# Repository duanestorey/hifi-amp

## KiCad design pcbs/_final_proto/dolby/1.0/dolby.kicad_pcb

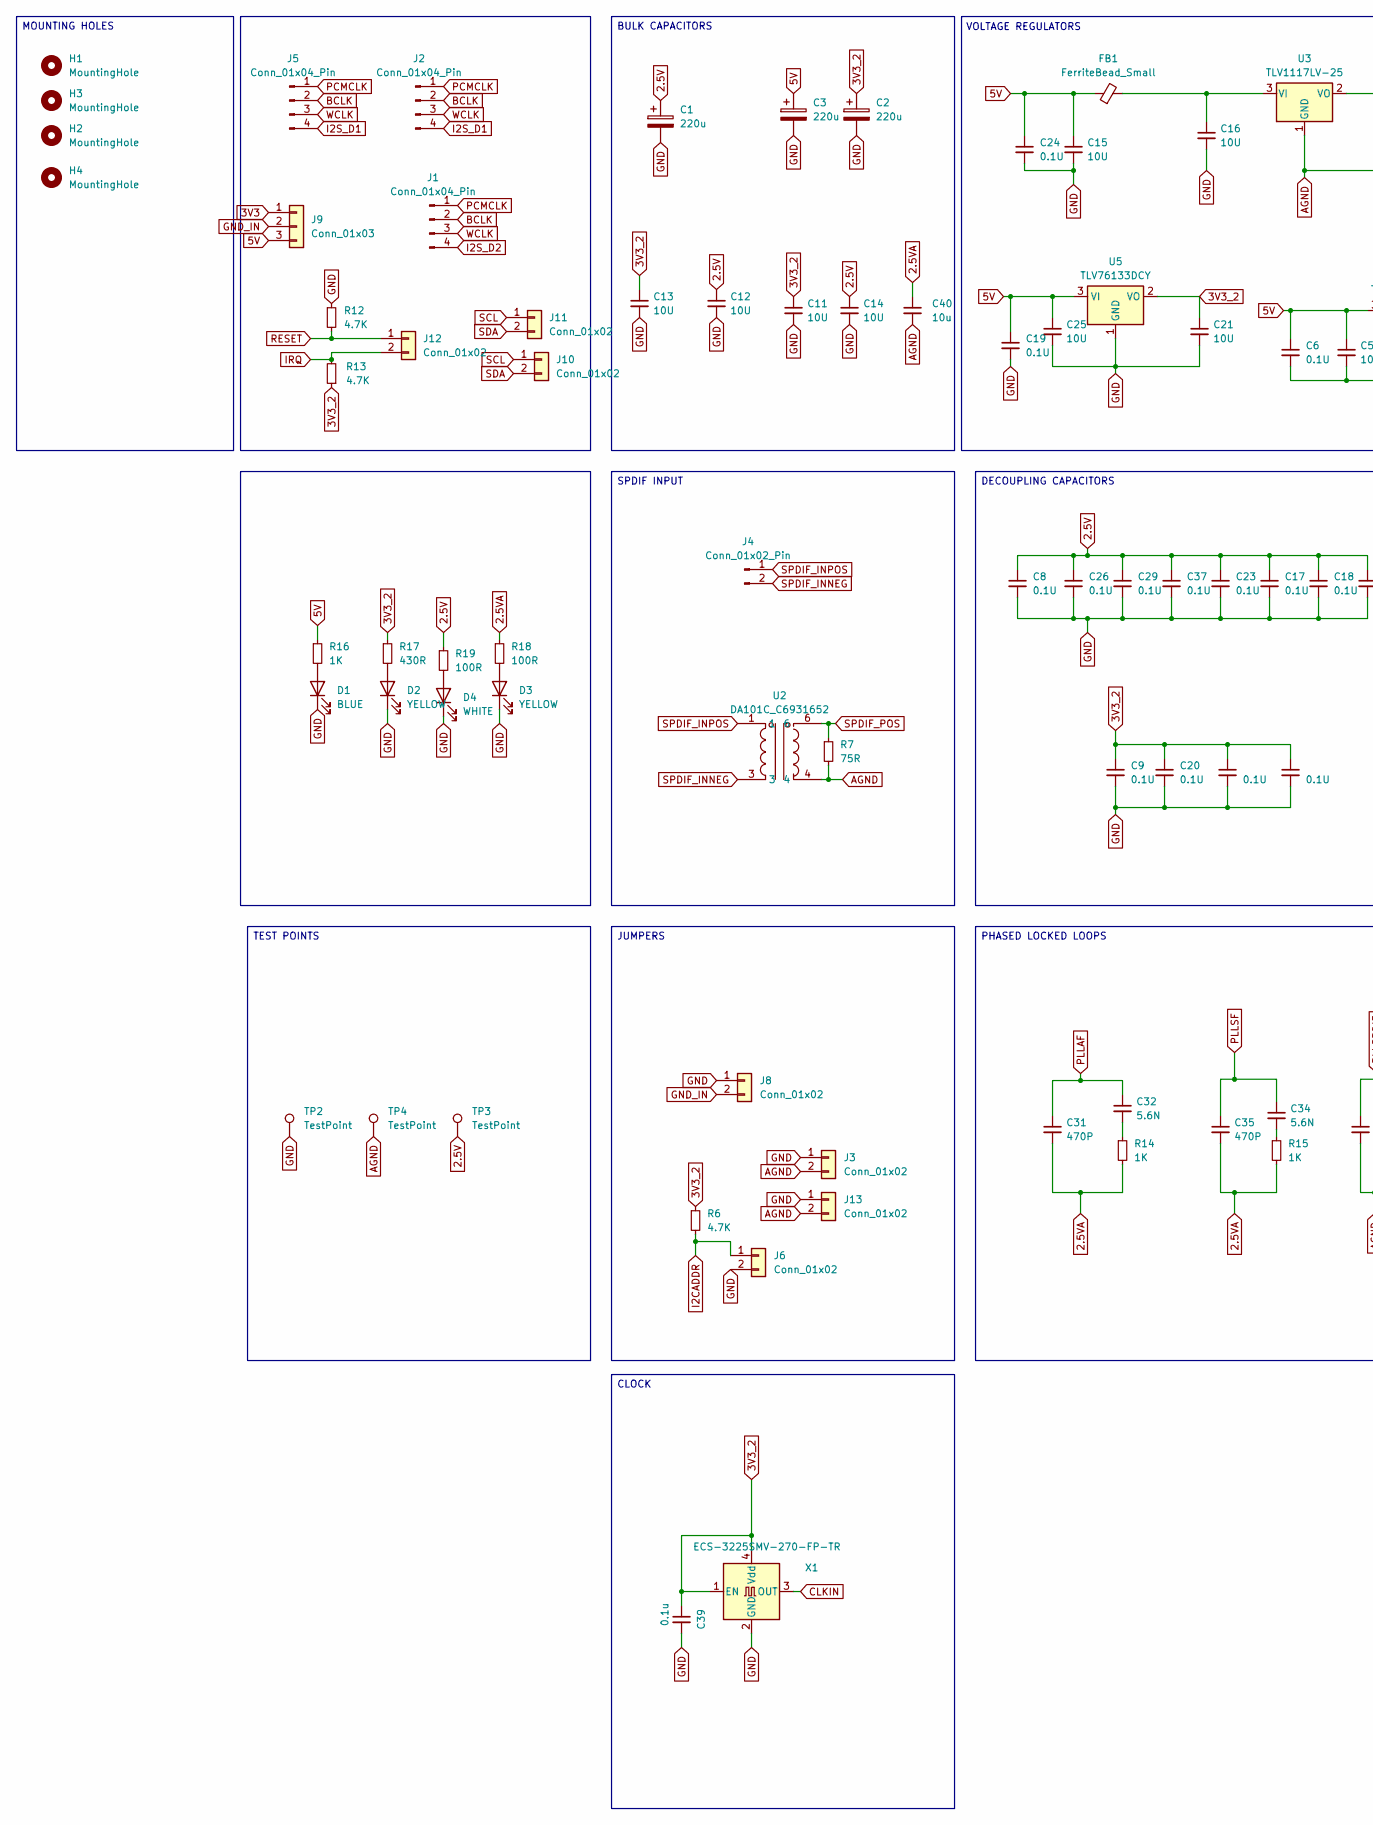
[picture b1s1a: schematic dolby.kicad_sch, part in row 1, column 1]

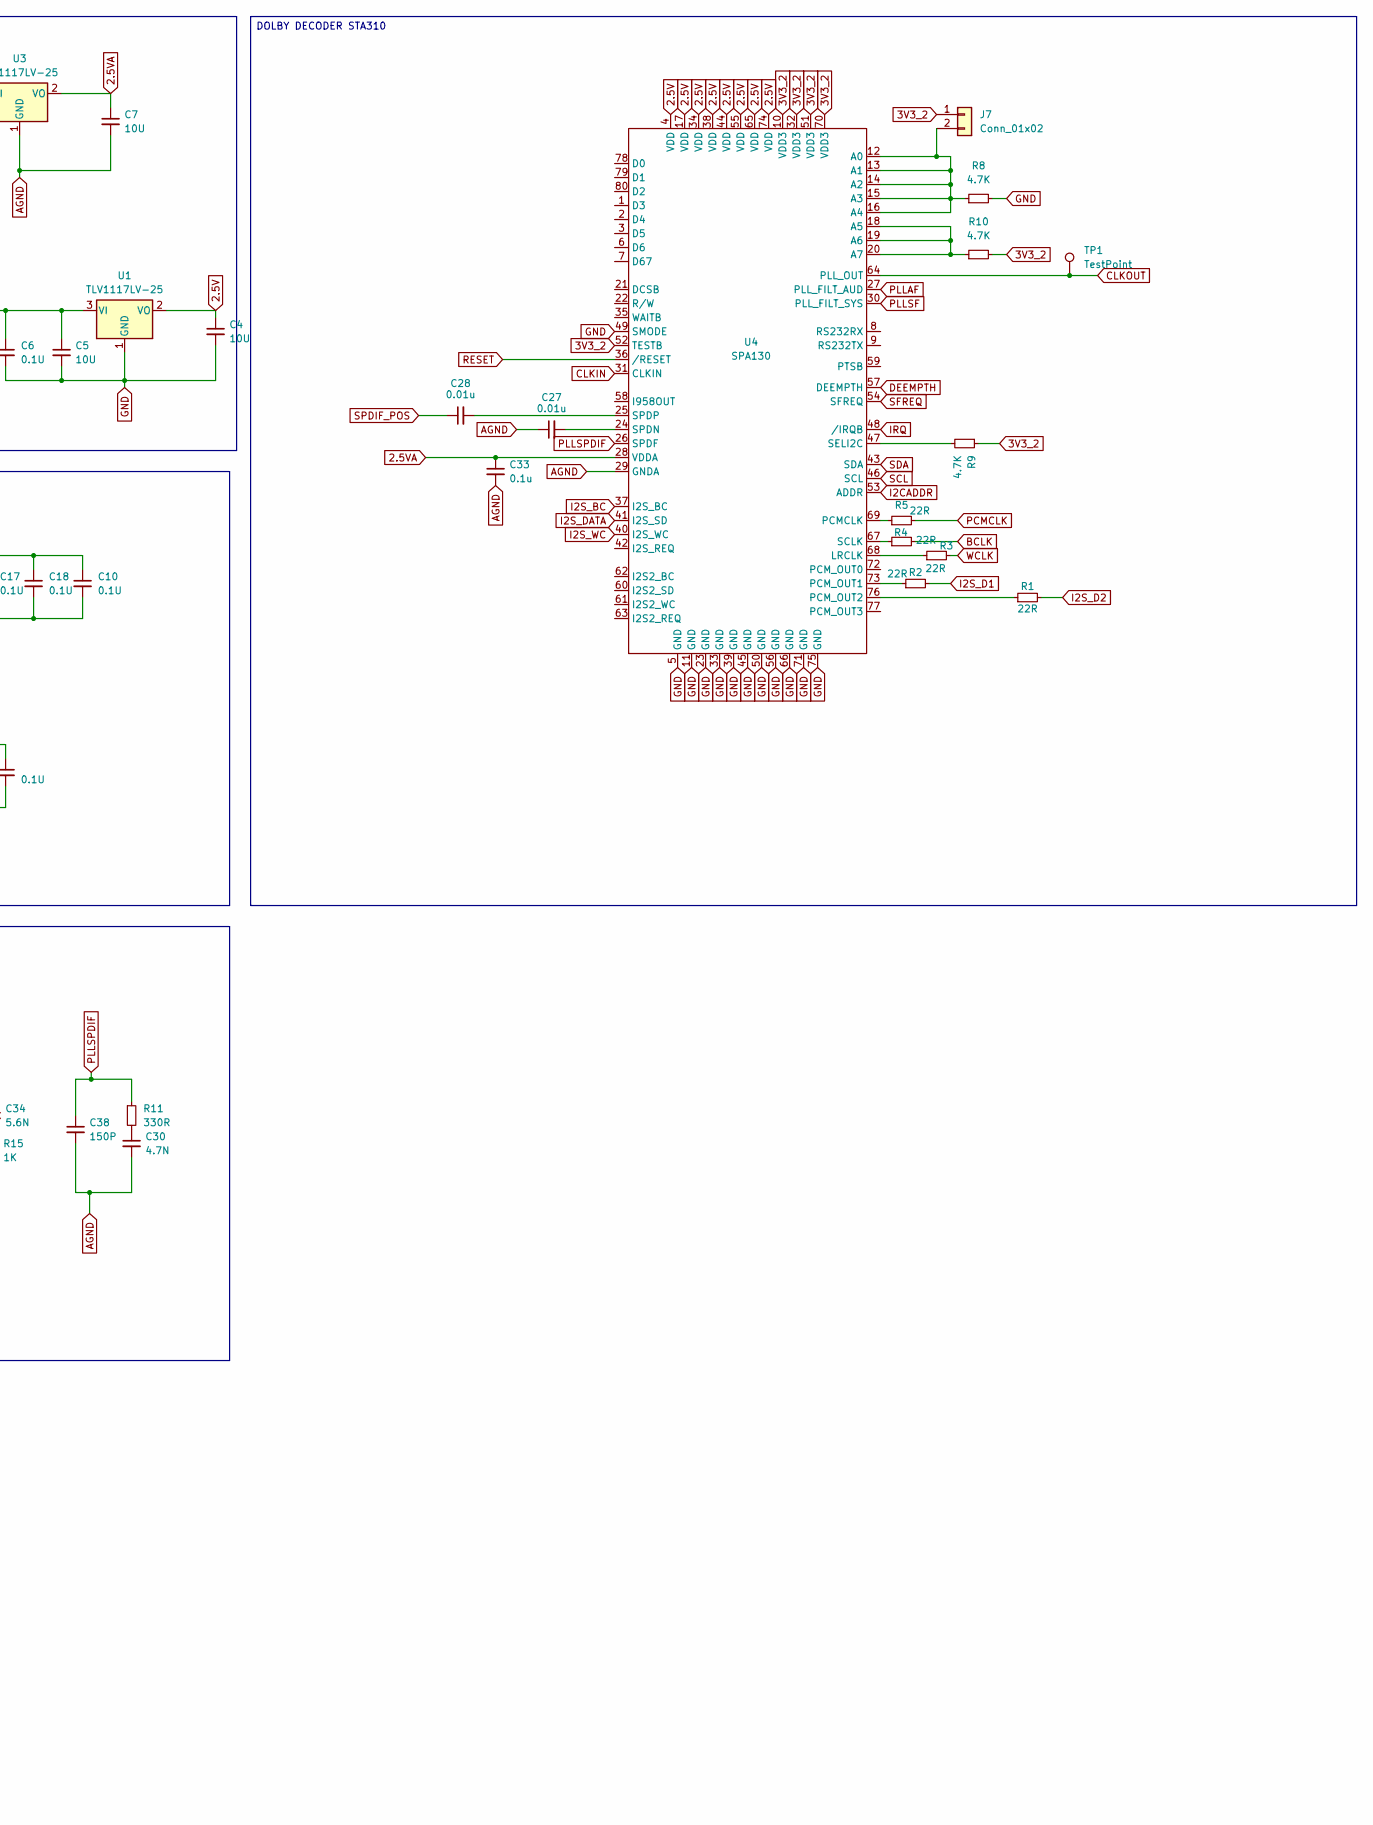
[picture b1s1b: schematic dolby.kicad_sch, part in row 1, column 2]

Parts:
C1, C2, C3: 220u; CP_Radial_D6.3mm_P2.50mm
C4, C5, C7, C11, C12, C13, C14, C15, C16, C21, C25: 10U; C_1206_3216Metric_Pad1.33x1.80mm_HandSolder
C6, C8, C9, C10, C17, C18, C19, C20, C22, C23, C24, C26, C29, C36, C37: 0.1U; C_0805_2012Metric_Pad1.18x1.45mm_HandSolder
C27, C28: 0.01u; C_0805_2012Metric_Pad1.18x1.45mm_HandSolder
C30: 4.7N; C_0805_2012Metric_Pad1.18x1.45mm_HandSolder
C31, C35: 470P; C_0805_2012Metric_Pad1.18x1.45mm_HandSolder
C32, C34: 5.6N; C_0805_2012Metric_Pad1.18x1.45mm_HandSolder
C33, C39: 0.1u; C_0805_2012Metric_Pad1.18x1.45mm_HandSolder
C38: 150P; C_0805_2012Metric_Pad1.18x1.45mm_HandSolder
C40: 10u; C_1206_3216Metric_Pad1.33x1.80mm_HandSolder
D1: BLUE; LED_0805_2012Metric_Pad1.15x1.40mm_HandSolder
D2, D3: YELLOW; LED_0805_2012Metric_Pad1.15x1.40mm_HandSolder
D4: WHITE; LED_0805_2012Metric_Pad1.15x1.40mm_HandSolder
FB1: FerriteBead_Small; R_0603_1608Metric_Pad0.98x0.95mm_HandSolder
H1, H2, H3, H4: MountingHole; MountingHole_3.2mm_M3_DIN965_Pad_TopBottom
J1, J2: Conn_01x04_Pin; JST_PH_B4B-PH-K_1x04_P2.00mm_Vertical
J3, J6, J7, J8, J13: Conn_01x02; PinHeader_1x02_P2.54mm_Vertical
J4: Conn_01x02_Pin; JST_XH_B2B-XH-A_1x02_P2.50mm_Vertical
J5: Conn_01x04_Pin; PinHeader_1x04_P2.54mm_Vertical
J9: Conn_01x03; JST_PH_B3B-PH-K_1x03_P2.00mm_Vertical
J10, J11, J12: Conn_01x02; JST_PH_B2B-PH-K_1x02_P2.00mm_Vertical
R1, R2, R3, R4, R5: 22R; R_0805_2012Metric_Pad1.20x1.40mm_HandSolder
R6, R8, R9, R10, R12, R13: 4.7K; R_0603_1608Metric_Pad0.98x0.95mm_HandSolder
R7: 75R; R_0805_2012Metric_Pad1.20x1.40mm_HandSolder
R11: 330R; R_0603_1608Metric_Pad0.98x0.95mm_HandSolder
R14, R15: 1K; R_0603_1608Metric_Pad0.98x0.95mm_HandSolder
R16: 1K; R_0805_2012Metric_Pad1.20x1.40mm_HandSolder
R17: 430R; R_0805_2012Metric_Pad1.20x1.40mm_HandSolder
R18, R19: 100R; R_0805_2012Metric_Pad1.20x1.40mm_HandSolder
TP1, TP2, TP3, TP4: TestPoint; TestPoint_THTPad_D2.0mm_Drill1.0mm
U1, U3: TLV1117LV-25; SOT-223-3_TabPin2
U2: DA101C_C6931652; XFMR-TH_4P-L9.5-W9.0-P5.08-LS10.2_C9900096976; LCSC Part C6931652
U4: SPA130; LQFP-80_14x14mm_P0.65mm
U5: TLV76133DCY; SOT-223-3_TabPin2
X1: ECS-3225SMV-270-FP-TR; Oscillator_SMD_EuroQuartz_XO32-4Pin_3.2x2.5mm_HandSoldering

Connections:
2.5V: C1.1, C4.1, C8.1, C10.1, C12.1, C14.1, C17.1, C18.1, C23.1, C26.1, C29.1, C37.1, R19.1, TP3.1, U1.2 (VO), U4.4 (VDD), U4.17 (VDD), U4.34 (VDD), U4.38 (VDD), U4.44 (VDD), U4.55 (VDD), U4.65 (VDD), U4.74 (VDD)
2.5VA: C7.1, C31.2, C33.1, C35.2, C40.1, R14.2, R15.2, R18.1, U3.2 (VO), U4.28 (VDDA)
3V3: J9.1
3V3_2: C2.1, C9.1, C11.1, C13.1, C20.1, C21.1, C22.1, C36.1, C39.1, J7.1, R6.1, R9.1, R10.2, R13.1, R17.1, U4.10 (VDD3), U4.32 (VDD3), U4.51 (VDD3), U4.52 (TESTB), U4.70 (VDD3), U5.2 (VO), X1.1 (EN), X1.4 (Vdd)
5V: C3.1, C5.1, C6.1, C15.1, C19.1, C24.1, C25.1, FB1.1, J9.3, R16.1, U1.3 (VI), U5.3 (VI)
AGND: C7.2, C27.1, C30.2, C33.2, C38.2, C40.2, J3.2, J13.2, R7.2, TP4.1, U2.4, U3.1 (GND), U4.29 (GNDA)
BCLK: J1.2, J2.2, J5.2, R4.2
CLKIN: U4.31 (CLKIN), X1.3 (OUT)
CLKOUT: TP1.1, U4.64 (PLL_OUT)
DEEMPTH: U4.57 (DEEMPTH)
GND: C1.2, C2.2, C3.2, C4.2, C5.2, C6.2, C8.2, C9.2, C10.2, C11.2, C12.2, C13.2, C14.2, C15.2, C16.2, C17.2, C18.2, C19.2, C20.2, C21.2, C22.2, C23.2, C24.2, C25.2, C26.2, C29.2, C36.2, C37.2, C39.2, D1.1 (K), D2.1 (K), D3.1 (K), D4.1 (K), J3.1, J6.2, J8.1, J13.1, R8.2, R12.1, TP2.1, U1.1 (GND), U4.5 (GND), U4.11 (GND), U4.23 (GND), U4.33 (GND), U4.39 (GND), U4.45 (GND), U4.49 (SMODE), U4.50 (GND), U4.56 (GND), U4.66 (GND), U4.71 (GND), U4.75 (GND), U5.1 (GND), X1.2 (GND)
GND_IN: J8.2, J9.2
I2CADDR: J6.1, R6.2, U4.53 (ADDR)
I2S_BC: U4.37 (I2S_BC)
I2S_D1: J2.4, J5.4, R2.2
I2S_D2: J1.4, R1.2
I2S_DATA: U4.41 (I2S_SD)
I2S_WC: U4.40 (I2S_WC)
IRQ: J12.2, R13.2, U4.48 (/IRQB)
unnamed: C30.1, R11.2
unnamed: C32.2, R14.1
unnamed: C34.2, R15.1
unnamed: D1.2 (A), R16.2
unnamed: D2.2 (A), R17.2
unnamed: D3.2 (A), R18.2
unnamed: D4.2 (A), R19.2
unnamed: J7.2, R8.1, U4.12 (A0), U4.13 (A1), U4.14 (A2), U4.15 (A3), U4.16 (A4)
unnamed: C16.1, FB1.2, U3.3 (VI)
unnamed: R10.1, U4.18 (A5), U4.19 (A6), U4.20 (A7)
unnamed: R3.1, U4.68 (LRCLK)
unnamed: R5.1, U4.69 (PCMCLK)
unnamed: R2.1, U4.73 (PCM_OUT1)
unnamed: R1.1, U4.76 (PCM_OUT2)
unnamed: R4.1, U4.67 (SCLK)
unnamed: R9.2, U4.47 (SELI2C)
unnamed: C27.2, U4.24 (SPDN)
unnamed: C28.2, U4.25 (SPDP)
PCMCLK: J1.1, J2.1, J5.1, R5.2
PLLAF: C31.1, C32.1, U4.27 (PLL_FILT_AUD)
PLLSF: C34.1, C35.1, U4.30 (PLL_FILT_SYS)
PLLSPDIF: C38.1, R11.1, U4.26 (SPDF)
RESET: J12.1, R12.2, U4.36 (/RESET)
SCL: J10.1, J11.1, U4.46 (SCL)
SDA: J10.2, J11.2, U4.43 (SDA)
SFREQ: U4.54 (SFREQ)
SPDIF_INNEG: J4.2, U2.3
SPDIF_INPOS: J4.1, U2.1
SPDIF_POS: C28.1, R7.1, U2.6
WCLK: J1.3, J2.3, J5.3, R3.2

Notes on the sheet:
VOLTAGE REGULATORS
CLOCK
JUMPERS
TEST POINTS
DOLBY DECODER STA310
BULK CAPACITORS
PHASED LOCKED LOOPS
SPDIF INPUT
MOUNTING HOLES
DECOUPLING CAPACITORS

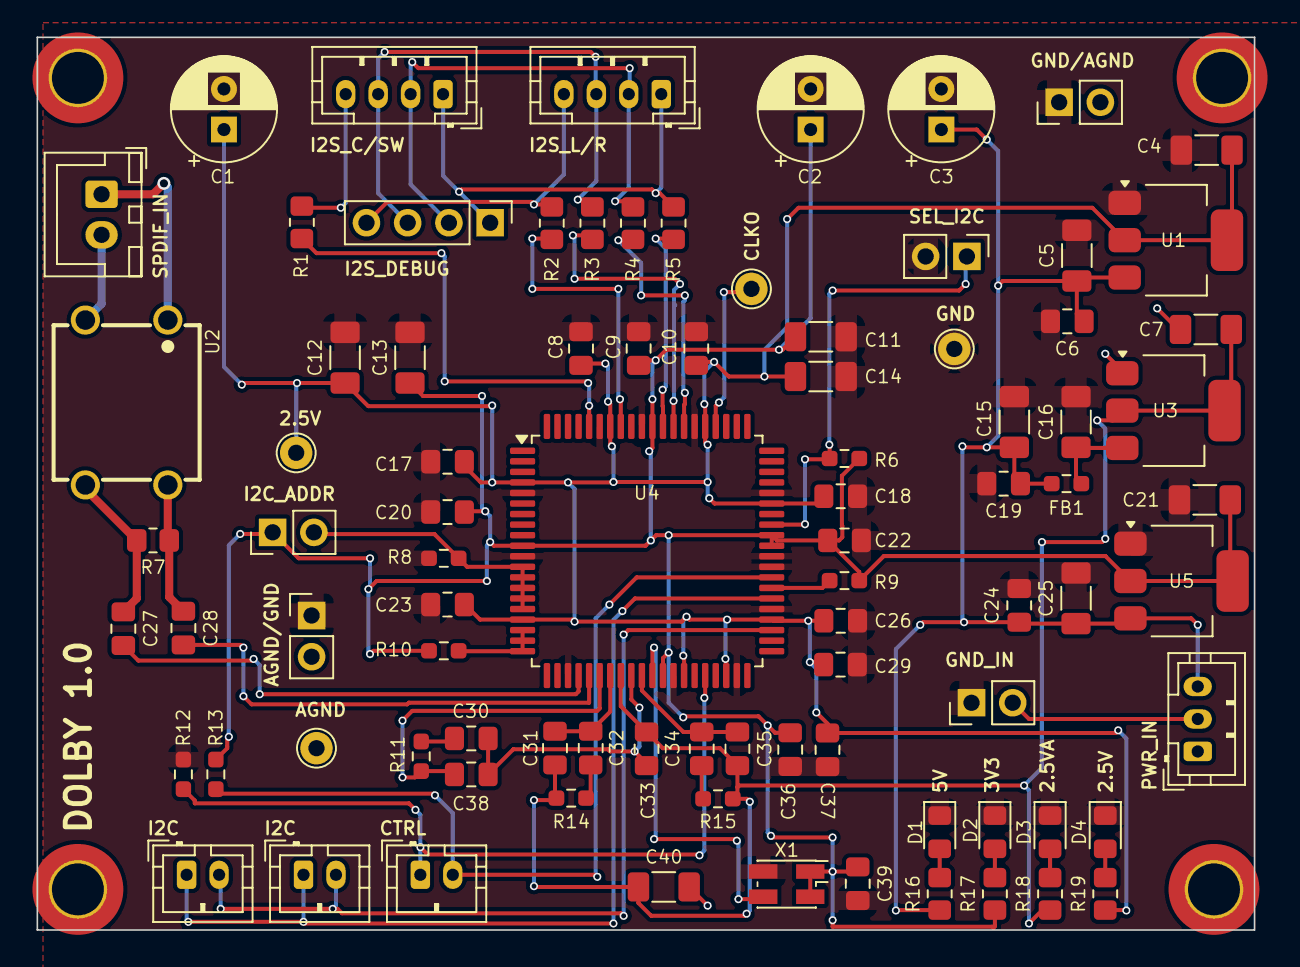
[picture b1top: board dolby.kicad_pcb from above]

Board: 2 copper layers, 75.0 x 55.0 mm, 91 parts (0 on the bottom side), 43 nets.

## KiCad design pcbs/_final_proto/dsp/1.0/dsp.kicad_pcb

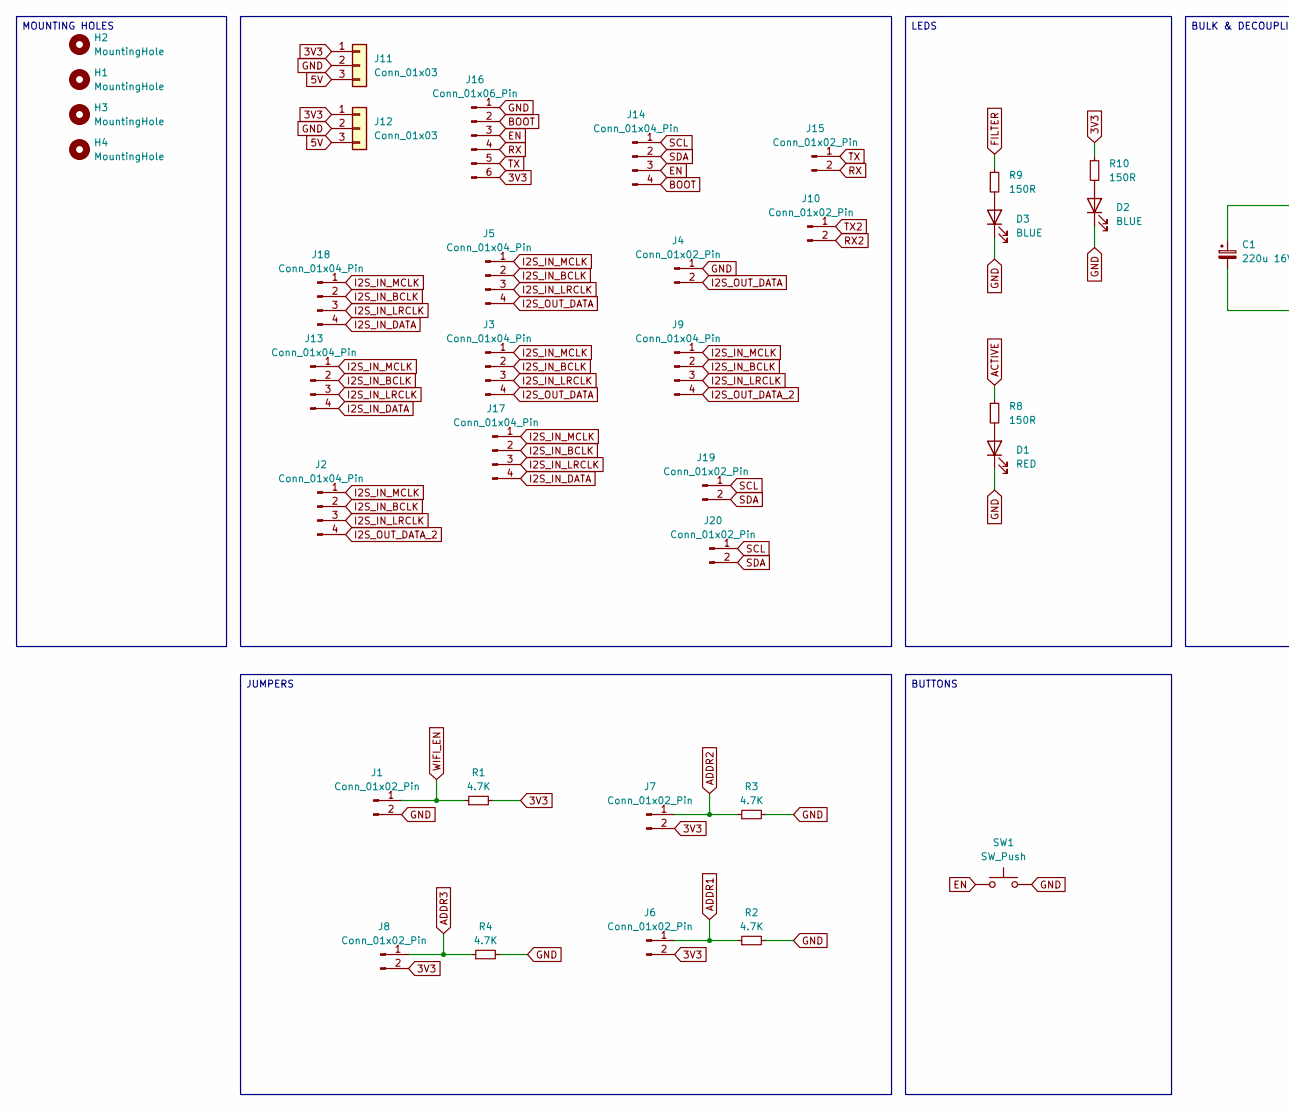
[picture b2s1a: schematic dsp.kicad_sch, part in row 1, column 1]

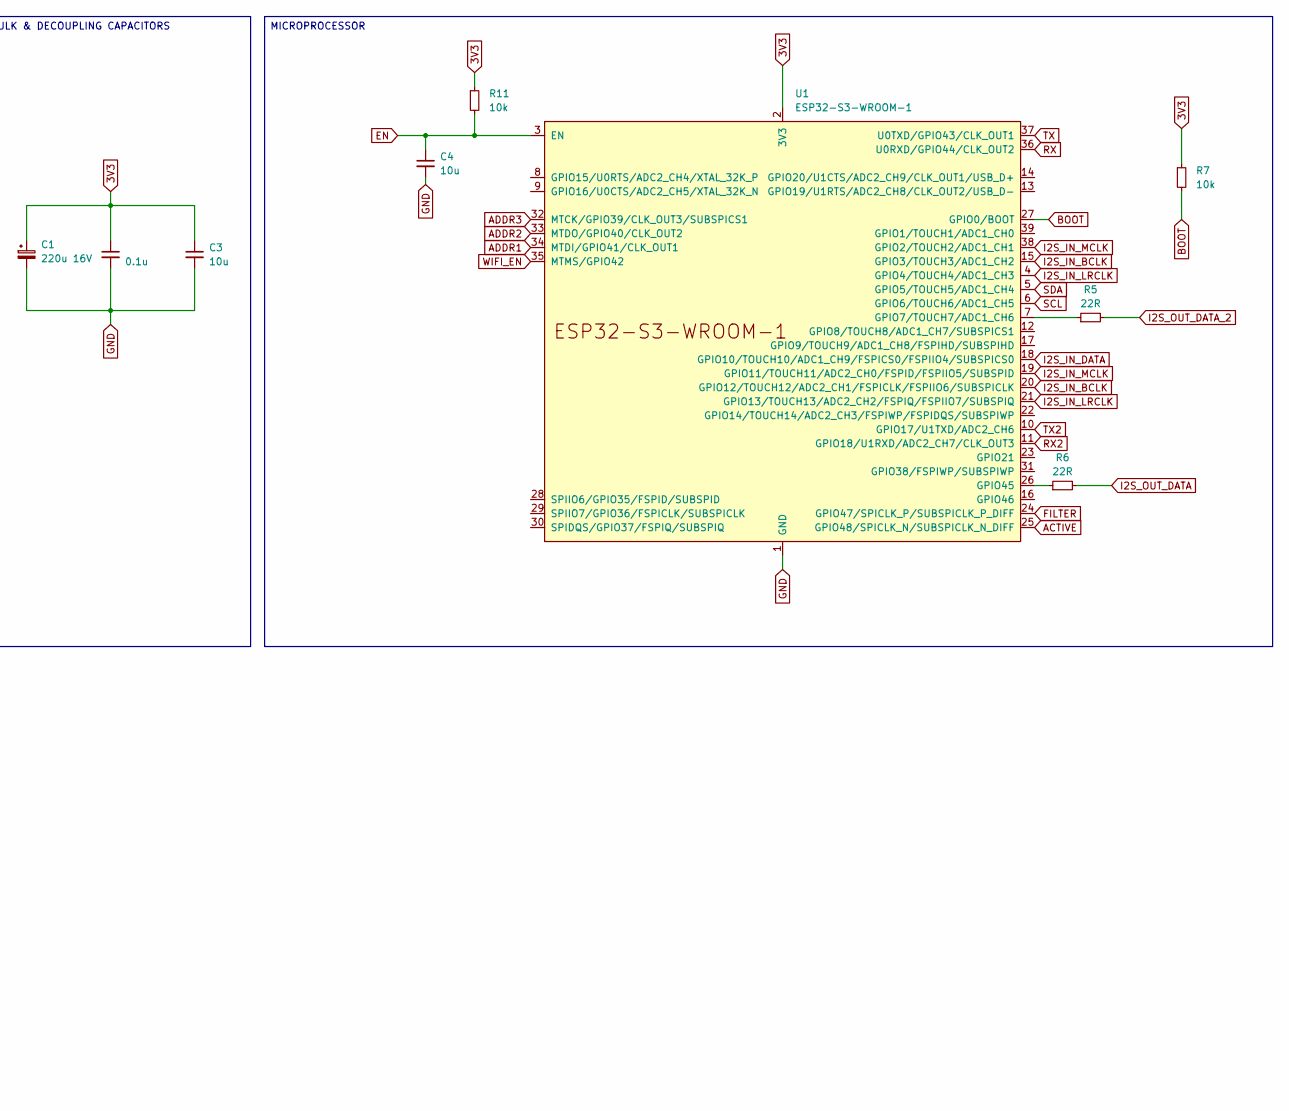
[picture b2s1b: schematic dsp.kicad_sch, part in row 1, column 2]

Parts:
C1: 220u 16V; CP_Radial_D6.3mm_P2.50mm
C2: 0.1u; C_0805_2012Metric_Pad1.18x1.45mm_HandSolder
C3, C4: 10u; C_1206_3216Metric_Pad1.33x1.80mm_HandSolder
D1: RED; D_0805_2012Metric_Pad1.15x1.40mm_HandSolder; LCSC C84259
D2, D3: BLUE; D_0805_2012Metric_Pad1.15x1.40mm_HandSolder; LCSC C84259
H1, H2, H3, H4: MountingHole; MountingHole_3.2mm_M3_DIN965_Pad_TopOnly
J1, J6, J7, J8: Conn_01x02_Pin; PinHeader_1x02_P2.54mm_Vertical
J2, J3, J13, J14, J17: Conn_01x04_Pin; JST_PH_B4B-PH-K_1x04_P2.00mm_Vertical
J4, J10, J15, J19, J20: Conn_01x02_Pin; JST_PH_B2B-PH-K_1x02_P2.00mm_Vertical
J5, J9, J18: Conn_01x04_Pin; PinHeader_1x04_P2.54mm_Vertical
J11, J12: Conn_01x03; JST_PH_B3B-PH-K_1x03_P2.00mm_Vertical
J16: Conn_01x06_Pin; PinHeader_1x06_P2.54mm_Vertical
R1, R2, R3, R4: 4.7K; R_0805_2012Metric_Pad1.20x1.40mm_HandSolder; LCSC C23162
R5, R6: 22R; R_0805_2012Metric_Pad1.20x1.40mm_HandSolder; Mouser 603-RT0805FRE0722RL
R7, R11: 10k; R_0805_2012Metric_Pad1.20x1.40mm_HandSolder; LCSC C23162
R8, R9, R10: 150R; R_0805_2012Metric_Pad1.20x1.40mm_HandSolder; LCSC C22808
SW1: SW_Push; Button Aliexpress 4x4
U1: ESP32-S3-WROOM-1; Mouser 356-ESP32S3WRM1N16R8

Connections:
3V3: C1.1, C2.1, C3.1, J6.2, J7.2, J8.2, J11.1, J12.1, J16.6, R1.2, R7.1, R10.1, R11.1, U1.2 (3V3)
5V: J11.3, J12.3
ACTIVE: R8.1, U1.25 (GPIO48/SPICLK_N/SUBSPICLK_N_DIFF)
ADDR1: J6.1, R2.1, U1.34 (MTDI/GPIO41/CLK_OUT1)
ADDR2: J7.1, R3.1, U1.33 (MTDO/GPIO40/CLK_OUT2)
ADDR3: J8.1, R4.1, U1.32 (MTCK/GPIO39/CLK_OUT3/SUBSPICS1)
BOOT: J14.4, J16.2, R7.2, U1.27 (GPIO0/BOOT)
EN: C4.1, J14.3, J16.3, R11.2, SW1.1, U1.3 (EN)
FILTER: R9.1, U1.24 (GPIO47/SPICLK_P/SUBSPICLK_P_DIFF)
GND: C1.2, C2.2, C3.2, C4.2, D1.1 (K), D2.1 (K), D3.1 (K), J1.2, J4.1, J11.2, J12.2, J16.1, R2.2, R3.2, R4.2, SW1.2, U1.1 (GND), U1.40 (GND), U1.41 (GND)
I2S_IN_BCLK: J2.2, J3.2, J5.2, J9.2, J13.2, J17.2, J18.2, U1.15 (GPIO3/TOUCH3/ADC1_CH2), U1.20 (GPIO12/TOUCH12/ADC2_CH1/FSPICLK/FSPIIO6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)
I2S_IN_DATA: J13.4, J17.4, J18.4, U1.18 (GPIO10/TOUCH10/ADC1_CH9/FSPICS0/FSPIIO4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)
I2S_IN_LRCLK: J2.3, J3.3, J5.3, J9.3, J13.3, J17.3, J18.3, U1.4 (GPIO4/TOUCH4/ADC1_CH3), U1.21 (GPIO13/TOUCH13/ADC2_CH2/FSPIQ/FSPIIO7/S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)
I2S_IN_MCLK: J2.1, J3.1, J5.1, J9.1, J13.1, J17.1, J18.1, U1.19 (GPIO11/TOUCH11/ADC2_CH0/FSPID/FSPIIO5/S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), U1.38 (GPIO2/TOUCH2/ADC1_CH1)
I2S_OUT_DATA: J3.4, J4.2, J5.4, R6.2
I2S_OUT_DATA_2: J2.4, J9.4, R5.2
unnamed: D1.2 (A), R8.2
unnamed: D2.2 (A), R10.2
unnamed: D3.2 (A), R9.2
unnamed: R5.1, U1.7 (GPIO7/TOUCH7/ADC1_CH6)
unnamed: R6.1, U1.26 (GPIO45)
RX: J15.2, J16.4, U1.36 (U0RXD/GPIO44/CLK_OUT2)
RX2: J10.2, U1.11 (GPIO18/U1RXD/ADC2_CH7/CLK_OUT3)
SCL: J14.1, J19.1, J20.1, U1.6 (GPIO6/TOUCH6/ADC1_CH5)
SDA: J14.2, J19.2, J20.2, U1.5 (GPIO5/TOUCH5/ADC1_CH4)
TX: J15.1, J16.5, U1.37 (U0TXD/GPIO43/CLK_OUT1)
TX2: J10.1, U1.10 (GPIO17/U1TXD/ADC2_CH6)
WIFI_EN: J1.1, R1.1, U1.35 (MTMS/GPIO42)

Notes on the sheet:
MOUNTING HOLES
MICROPROCESSOR
BUTTONS
LEDS
BULK & DECOUPLING CAPACITORS
JUMPERS

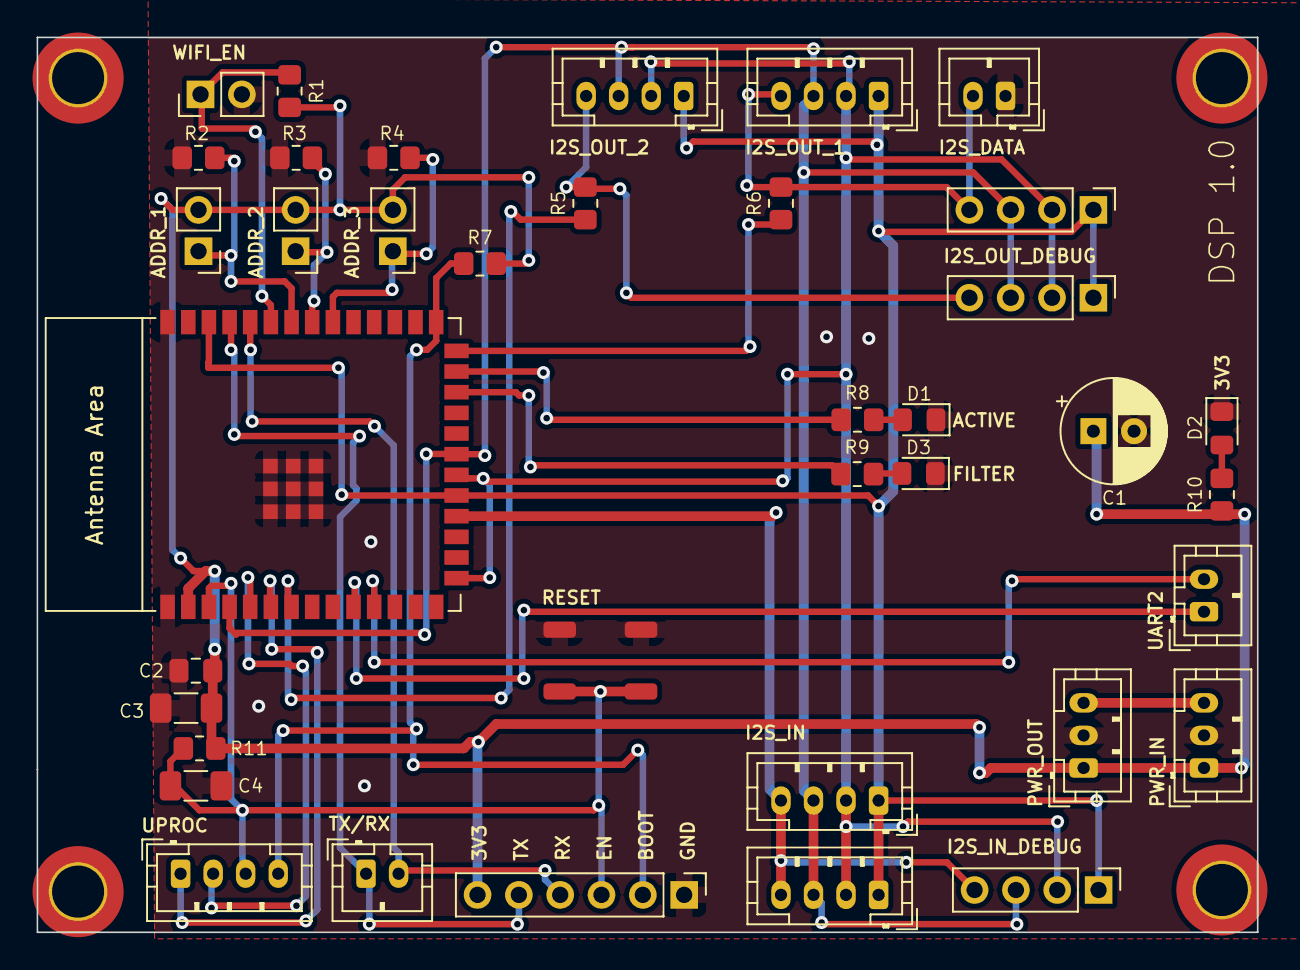
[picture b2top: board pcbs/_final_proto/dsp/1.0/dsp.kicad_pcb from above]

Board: 2 copper layers, 75.0 x 55.0 mm, 42 parts (0 on the bottom side), 28 nets.
